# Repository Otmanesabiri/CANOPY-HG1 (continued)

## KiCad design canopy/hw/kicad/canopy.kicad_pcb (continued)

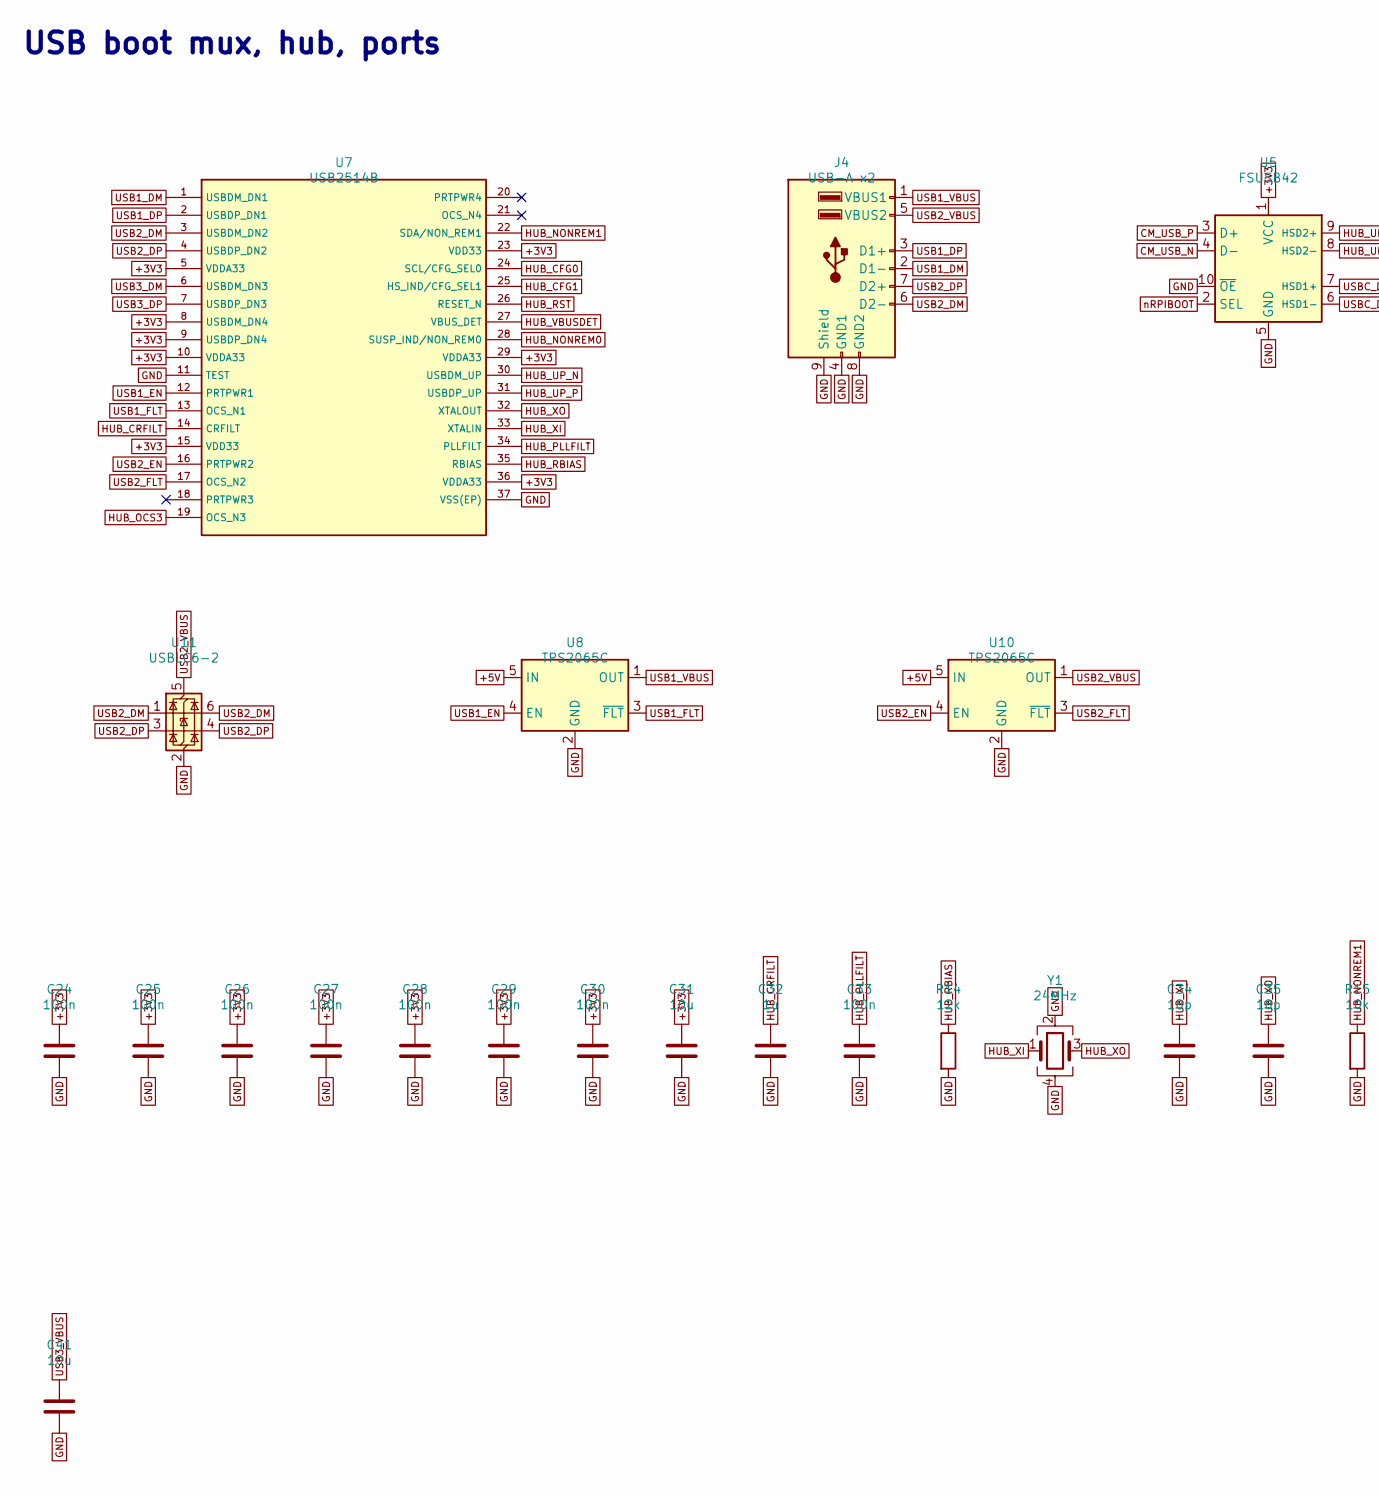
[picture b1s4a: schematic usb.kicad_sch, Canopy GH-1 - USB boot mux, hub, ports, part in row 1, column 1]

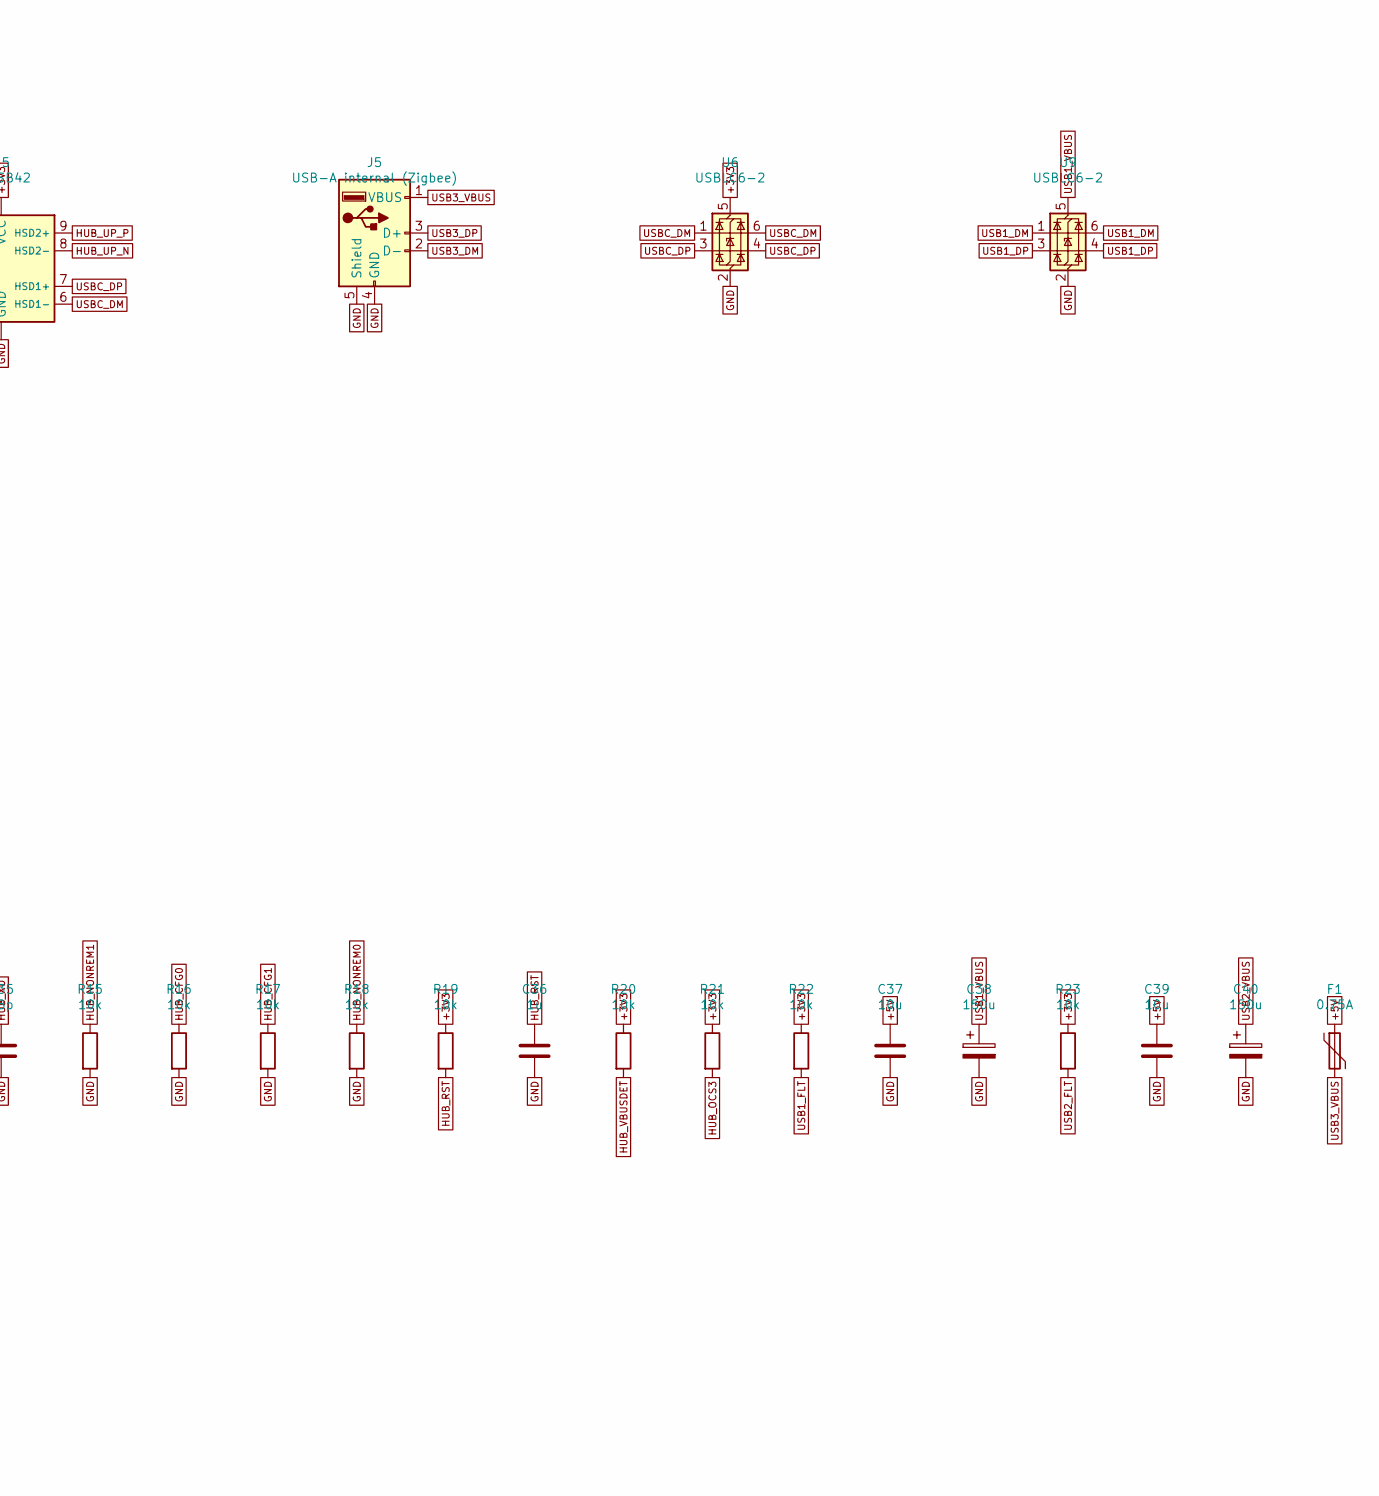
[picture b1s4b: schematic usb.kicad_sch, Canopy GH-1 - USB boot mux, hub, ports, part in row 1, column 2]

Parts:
C24, C25, C26, C27, C28, C29, C30, C33: 100n; C_0603_1608Metric; MPN GRM188R71H104KA93D
C31, C37, C39, C41: 10u; C_0603_1608Metric; MPN GRM188R61A106KE69D
C32, C36: 1u; C_0603_1608Metric; MPN CL10A105KB8NNNC
C34, C35: 18p; C_0603_1608Metric; MPN GRM1885C1H180JA01D
C38, C40: 150u; CP_EIA-3528-21_Kemet-B; MPN T520B157M006ATE070
F1: 0.75A; Fuse_1206_3216Metric; MPN 1206L075THYR
J4: USB-A x2; USB_A_Wuerth_61400826021_Horizontal_Stacked; MPN 61400826021
J5: USB-A internal (Zigbee); USB_A_Molex_105057_Vertical; MPN 105057-0001
R14: 12k; R_0603_1608Metric; MPN RC0603FR-0712KL
R15, R16, R17, R18, R19, R20, R21, R22, R23: 10k; R_0603_1608Metric; MPN RC0603FR-0710KL
U5: FSUSB42; MSOP-10_3x3mm_P0.5mm; MPN FSUSB42MUX
U6, U9, U11: USBLC6-2; SOT-23-6; MPN USBLC6-2SC6
U7: USB2514B; QFN-36-1EP_6x6mm_P0.5mm_EP3.7x3.7mm; MPN USB2514B-I/M2
U8, U10: TPS2065C; SOT-23-5; MPN TPS2065CDBVR
Y1: 24MHz; Crystal_SMD_3225-4Pin_3.2x2.5mm; MPN ABM8-24.000MHZ-B2-T

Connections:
+3V3: C24.1, C25.1, C26.1, C27.1, C28.1, C29.1, C30.1, C31.1, R19.1, R20.1, R21.1, R22.1, R23.1, U5.1 (VCC), U6.5 (VBUS), U7.5 (VDDA33), U7.8 (USBDM_DN4), U7.9 (USBDP_DN4), U7.10 (VDDA33), U7.15 (VDD33), U7.23 (VDD33), U7.29 (VDDA33), U7.36 (VDDA33); also elsewhere on the board
+5V: C37.1, C39.1, F1.1, U8.5 (IN), U10.5 (IN); also elsewhere on the board
CM_USB_N: U5.4 (D-); also elsewhere on the board
CM_USB_P: U5.3 (D+); also elsewhere on the board
GND: C24.2, C25.2, C26.2, C27.2, C28.2, C29.2, C30.2, C31.2, C32.2, C33.2, C34.2, C35.2, C36.2, C37.2, C38.2, C39.2, C40.2, C41.2, J4.4 (GND1), J4.8 (GND2), J4.9 (Shield), J5.4 (GND), J5.5 (Shield), R14.2, R15.2, R16.2, R17.2, R18.2, U5.5 (GND), U5.10 (~OE), U6.2 (GND), U7.11 (TEST), U7.37 (VSS(EP)), U8.2 (GND), U9.2 (GND), U10.2 (GND), U11.2 (GND), Y1.2, Y1.4; also elsewhere on the board
HUB_CFG0: R16.1, U7.24 (SCL/CFG_SEL0)
HUB_CFG1: R17.1, U7.25 (HS_IND/CFG_SEL1)
HUB_CRFILT: C32.1, U7.14 (CRFILT)
HUB_NONREM0: R18.1, U7.28 (SUSP_IND/NON_REM0)
HUB_NONREM1: R15.1, U7.22 (SDA/NON_REM1)
HUB_OCS3: R21.2, U7.19 (OCS_N3)
HUB_PLLFILT: C33.1, U7.34 (PLLFILT)
HUB_RBIAS: R14.1, U7.35 (RBIAS)
HUB_RST: C36.1, R19.2, U7.26 (RESET_N)
HUB_UP_N: U5.8 (HSD2-), U7.30 (USBDM_UP)
HUB_UP_P: U5.9 (HSD2+), U7.31 (USBDP_UP)
HUB_VBUSDET: R20.2, U7.27 (VBUS_DET)
HUB_XI: C34.1, U7.33 (XTALIN), Y1.1
HUB_XO: C35.1, U7.32 (XTALOUT), Y1.3
USB1_DM: J4.2 (D1-), U7.1 (USBDM_DN1), U9.1 (I/O1), U9.6 (I/O1)
USB1_DP: J4.3 (D1+), U7.2 (USBDP_DN1), U9.3 (I/O2), U9.4 (I/O2)
USB1_EN: U7.12 (PRTPWR1), U8.4 (EN)
USB1_FLT: R22.2, U7.13 (OCS_N1), U8.3 (~FLT)
USB1_VBUS: C38.1, J4.1 (VBUS1), U8.1 (OUT), U9.5 (VBUS)
USB2_DM: J4.6 (D2-), U7.3 (USBDM_DN2), U11.1 (I/O1), U11.6 (I/O1)
USB2_DP: J4.7 (D2+), U7.4 (USBDP_DN2), U11.3 (I/O2), U11.4 (I/O2)
USB2_EN: U7.16 (PRTPWR2), U10.4 (EN)
USB2_FLT: R23.2, U7.17 (OCS_N2), U10.3 (~FLT)
USB2_VBUS: C40.1, J4.5 (VBUS2), U10.1 (OUT), U11.5 (VBUS)
USB3_DM: J5.2 (D-), U7.6 (USBDM_DN3)
USB3_DP: J5.3 (D+), U7.7 (USBDP_DN3)
USB3_VBUS: C41.1, F1.2, J5.1 (VBUS)
USBC_DM: U5.6 (HSD1-), U6.1 (I/O1), U6.6 (I/O1); also elsewhere on the board
USBC_DP: U5.7 (HSD1+), U6.3 (I/O2), U6.4 (I/O2); also elsewhere on the board
nRPIBOOT: U5.2 (SEL); also elsewhere on the board

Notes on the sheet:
USB boot mux, hub, ports

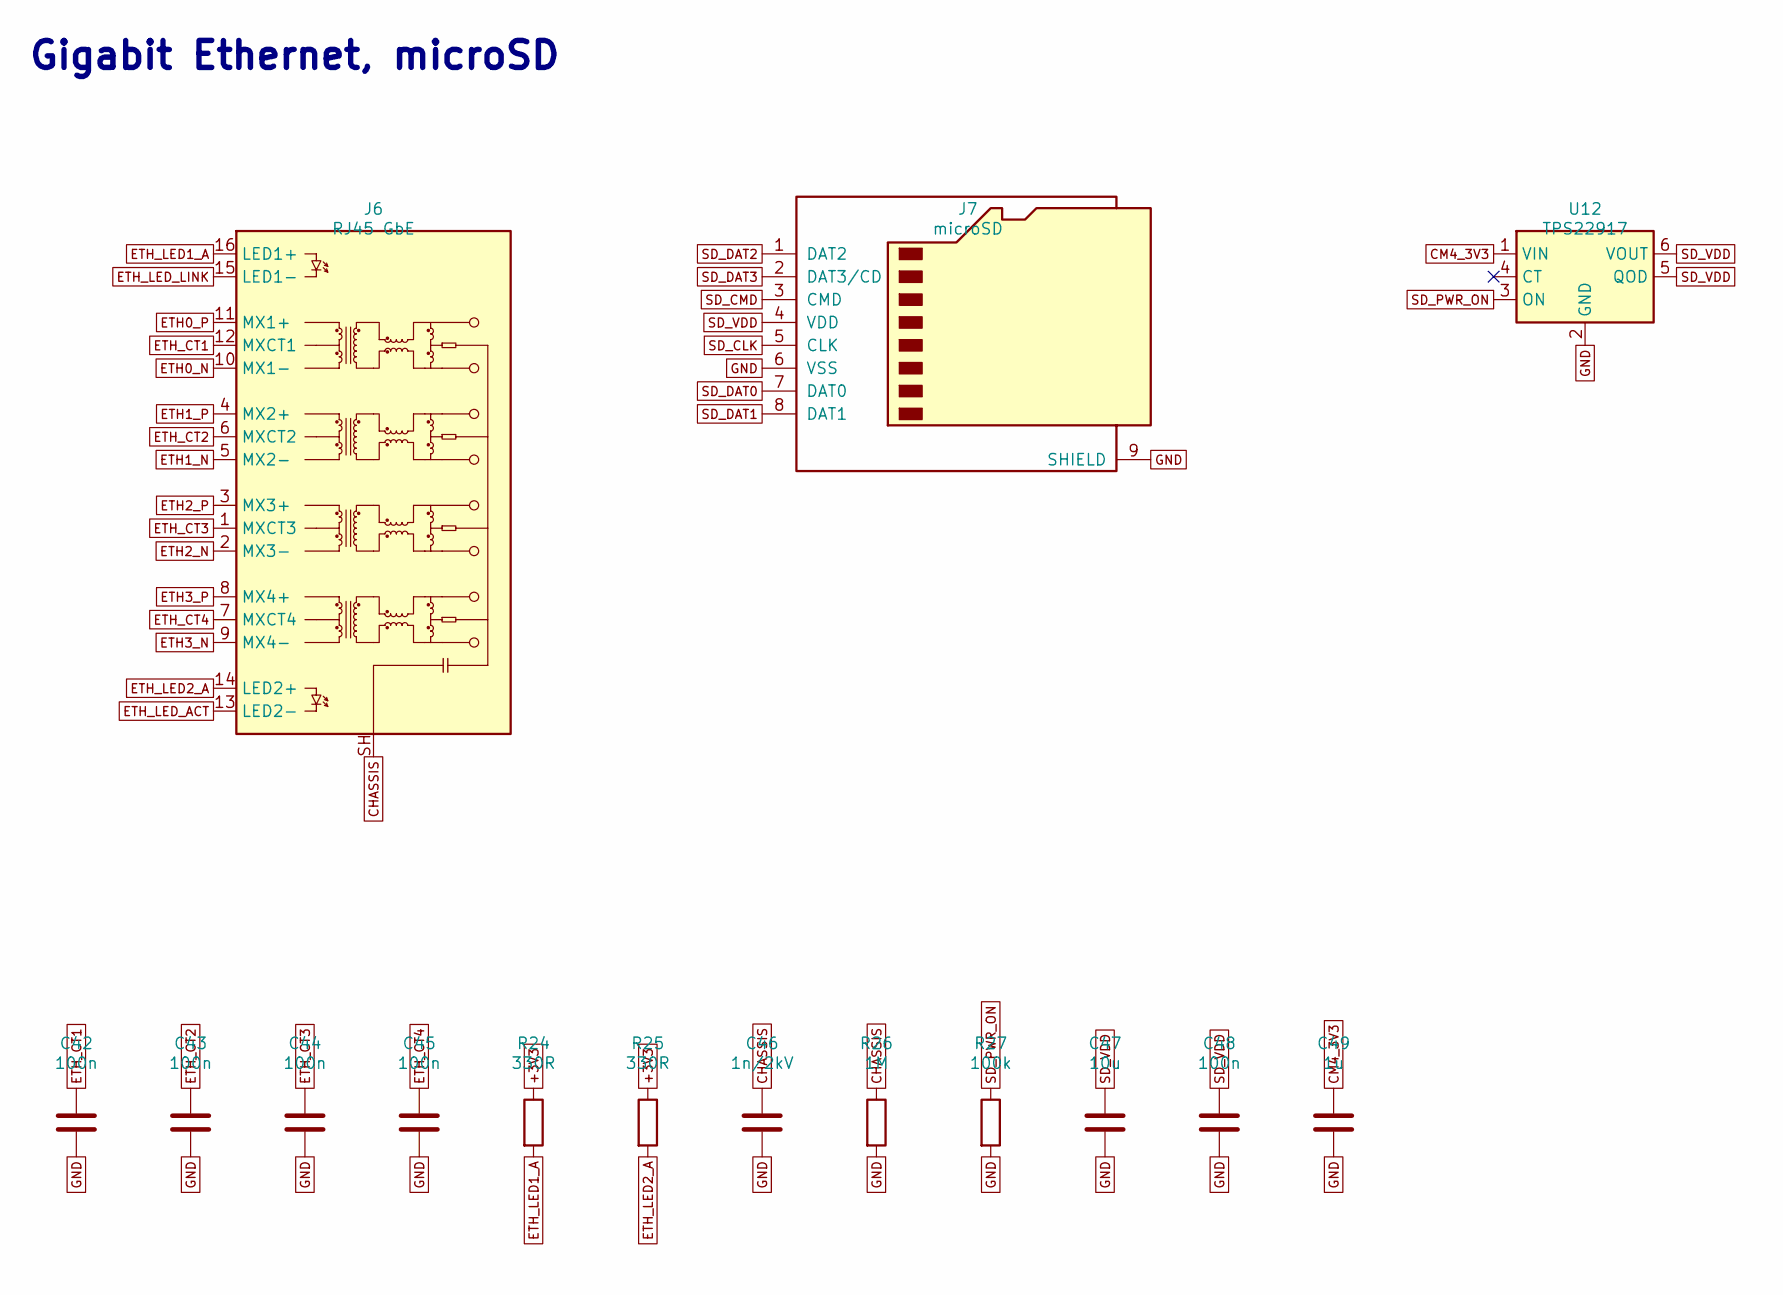
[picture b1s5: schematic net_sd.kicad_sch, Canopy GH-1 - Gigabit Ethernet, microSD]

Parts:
C42, C43, C44, C45, C48: 100n; C_0603_1608Metric; MPN GRM188R71H104KA93D
C46: 1n/2kV; C_1206_3216Metric; MPN C1206C102KGRACTU
C47: 10u; C_0603_1608Metric; MPN GRM188R61A106KE69D
C49: 1u; C_0603_1608Metric; MPN CL10A105KB8NNNC
J6: RJ45 GbE; RJ45_Pulse_JK0654219NL_Horizontal; MPN JK0654219NL
J7: microSD; microSD_HC_Molex_104031-0811; MPN 104031-0811
R24, R25: 330R; R_0603_1608Metric; MPN RC0603FR-07330RL
R26: 1M; R_0603_1608Metric; MPN RC0603FR-071ML
R27: 100k; R_0603_1608Metric; MPN RC0603FR-07100KL
U12: TPS22917; SOT-23-6; MPN TPS22917DBVR

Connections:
+3V3: R24.1, R25.1; also elsewhere on the board
CHASSIS: C46.1, J6.SH, R26.1
CM4_3V3: C49.1, U12.1 (VIN); also elsewhere on the board
ETH0_N: J6.10 (MX1-); also elsewhere on the board
ETH0_P: J6.11 (MX1+); also elsewhere on the board
ETH1_N: J6.5 (MX2-); also elsewhere on the board
ETH1_P: J6.4 (MX2+); also elsewhere on the board
ETH2_N: J6.2 (MX3-); also elsewhere on the board
ETH2_P: J6.3 (MX3+); also elsewhere on the board
ETH3_N: J6.9 (MX4-); also elsewhere on the board
ETH3_P: J6.8 (MX4+); also elsewhere on the board
ETH_CT1: C42.1, J6.12 (MXCT1)
ETH_CT2: C43.1, J6.6 (MXCT2)
ETH_CT3: C44.1, J6.1 (MXCT3)
ETH_CT4: C45.1, J6.7 (MXCT4)
ETH_LED1_A: J6.16 (LED1+), R24.2
ETH_LED2_A: J6.14 (LED2+), R25.2
ETH_LED_ACT: J6.13 (LED2-); also elsewhere on the board
ETH_LED_LINK: J6.15 (LED1-); also elsewhere on the board
GND: C42.2, C43.2, C44.2, C45.2, C46.2, C47.2, C48.2, C49.2, J7.6 (VSS), J7.9 (SHIELD), J7.10, J7.11, R26.2, R27.2, U12.2 (GND); also elsewhere on the board
SD_CLK: J7.5 (CLK); also elsewhere on the board
SD_CMD: J7.3 (CMD); also elsewhere on the board
SD_DAT0: J7.7 (DAT0); also elsewhere on the board
SD_DAT1: J7.8 (DAT1); also elsewhere on the board
SD_DAT2: J7.1 (DAT2); also elsewhere on the board
SD_DAT3: J7.2 (DAT3/CD); also elsewhere on the board
SD_PWR_ON: R27.1, U12.3 (ON); also elsewhere on the board
SD_VDD: C47.1, C48.1, J7.4 (VDD), U12.5 (QOD), U12.6 (VOUT)

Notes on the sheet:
Gigabit Ethernet, microSD

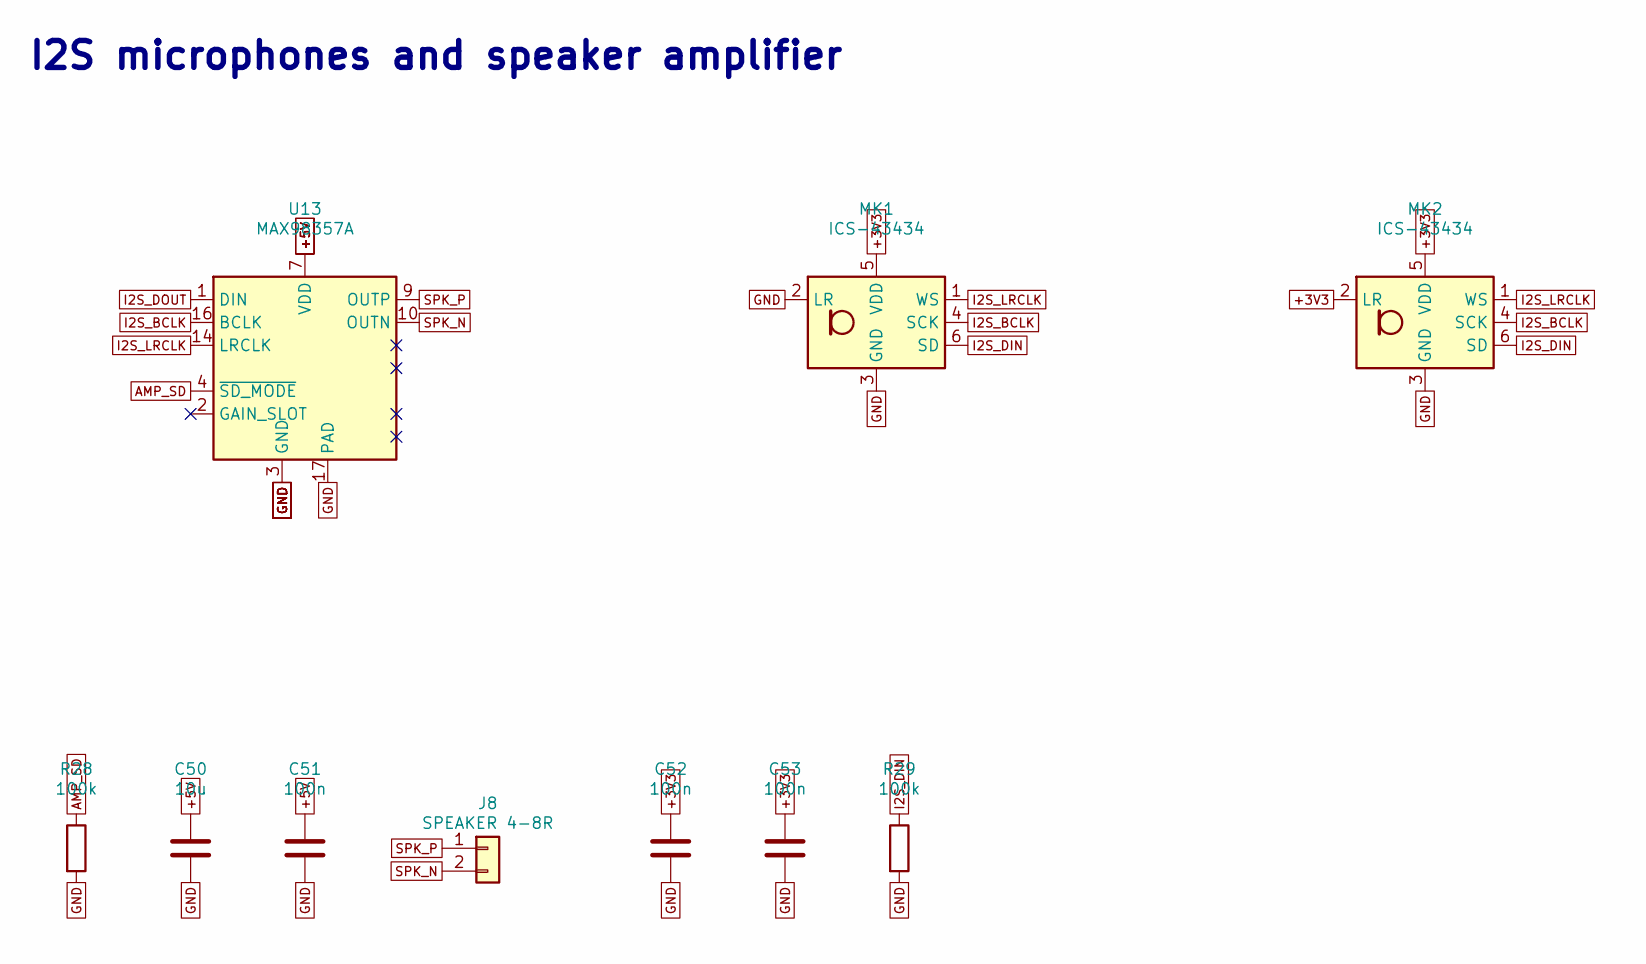
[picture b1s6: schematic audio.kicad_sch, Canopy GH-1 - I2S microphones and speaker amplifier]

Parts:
C50: 10u; C_0603_1608Metric; MPN GRM188R61A106KE69D
C51, C52, C53: 100n; C_0603_1608Metric; MPN GRM188R71H104KA93D
J8: SPEAKER 4-8R; JST_PH_S2B-PH-K_1x02_P2.00mm_Horizontal; MPN S2B-PH-K-S(LF)(SN)
MK1, MK2: ICS-43434; InvenSense_ICS-43434-6_3.5x2.65mm; MPN ICS-43434
R28, R29: 100k; R_0603_1608Metric; MPN RC0603FR-07100KL
U13: MAX98357A; TQFN-16-1EP_3x3mm_P0.5mm_EP1.23x1.23mm; MPN MAX98357AETE+T

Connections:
+3V3: C52.1, C53.1, MK1.5 (VDD), MK2.2 (LR), MK2.5 (VDD); also elsewhere on the board
+5V: C50.1, C51.1, U13.7 (VDD), U13.8 (VDD); also elsewhere on the board
AMP_SD: R28.1, U13.4 (~SD_MODE); also elsewhere on the board
GND: C50.2, C51.2, C52.2, C53.2, MK1.2 (LR), MK1.3 (GND), MK2.3 (GND), R28.2, R29.2, U13.3 (GND), U13.11 (GND), U13.15 (GND), U13.17 (PAD); also elsewhere on the board
I2S_BCLK: MK1.4 (SCK), MK2.4 (SCK), U13.16 (BCLK); also elsewhere on the board
I2S_DIN: MK1.6 (SD), MK2.6 (SD), R29.1; also elsewhere on the board
I2S_DOUT: U13.1 (DIN); also elsewhere on the board
I2S_LRCLK: MK1.1 (WS), MK2.1 (WS), U13.14 (LRCLK); also elsewhere on the board
SPK_N: J8.2, U13.10 (OUTN)
SPK_P: J8.1, U13.9 (OUTP)

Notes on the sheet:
I2S microphones and speaker amplifier

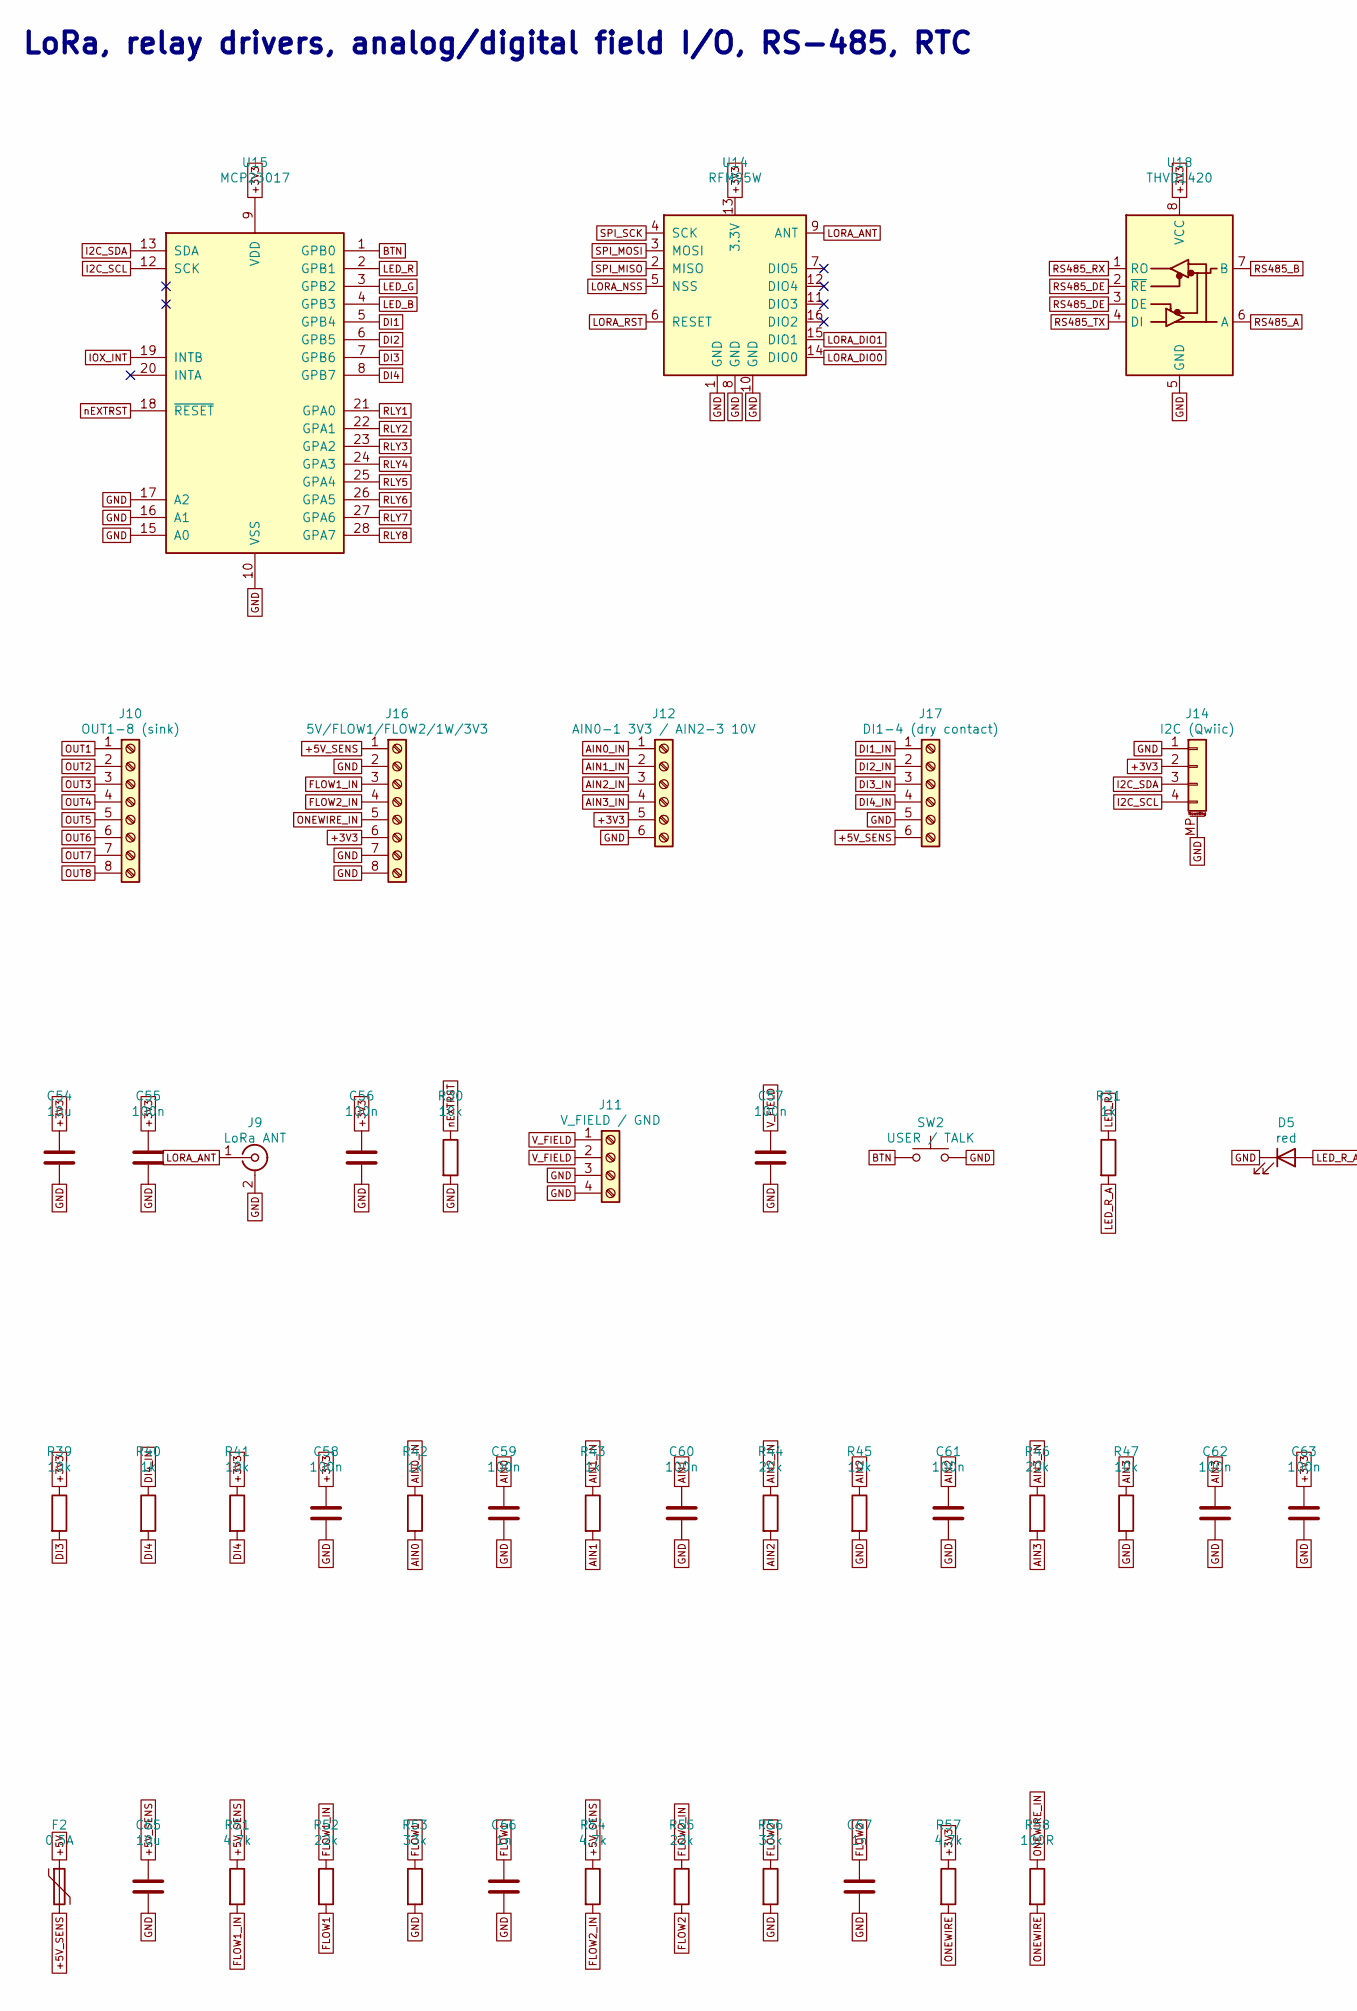
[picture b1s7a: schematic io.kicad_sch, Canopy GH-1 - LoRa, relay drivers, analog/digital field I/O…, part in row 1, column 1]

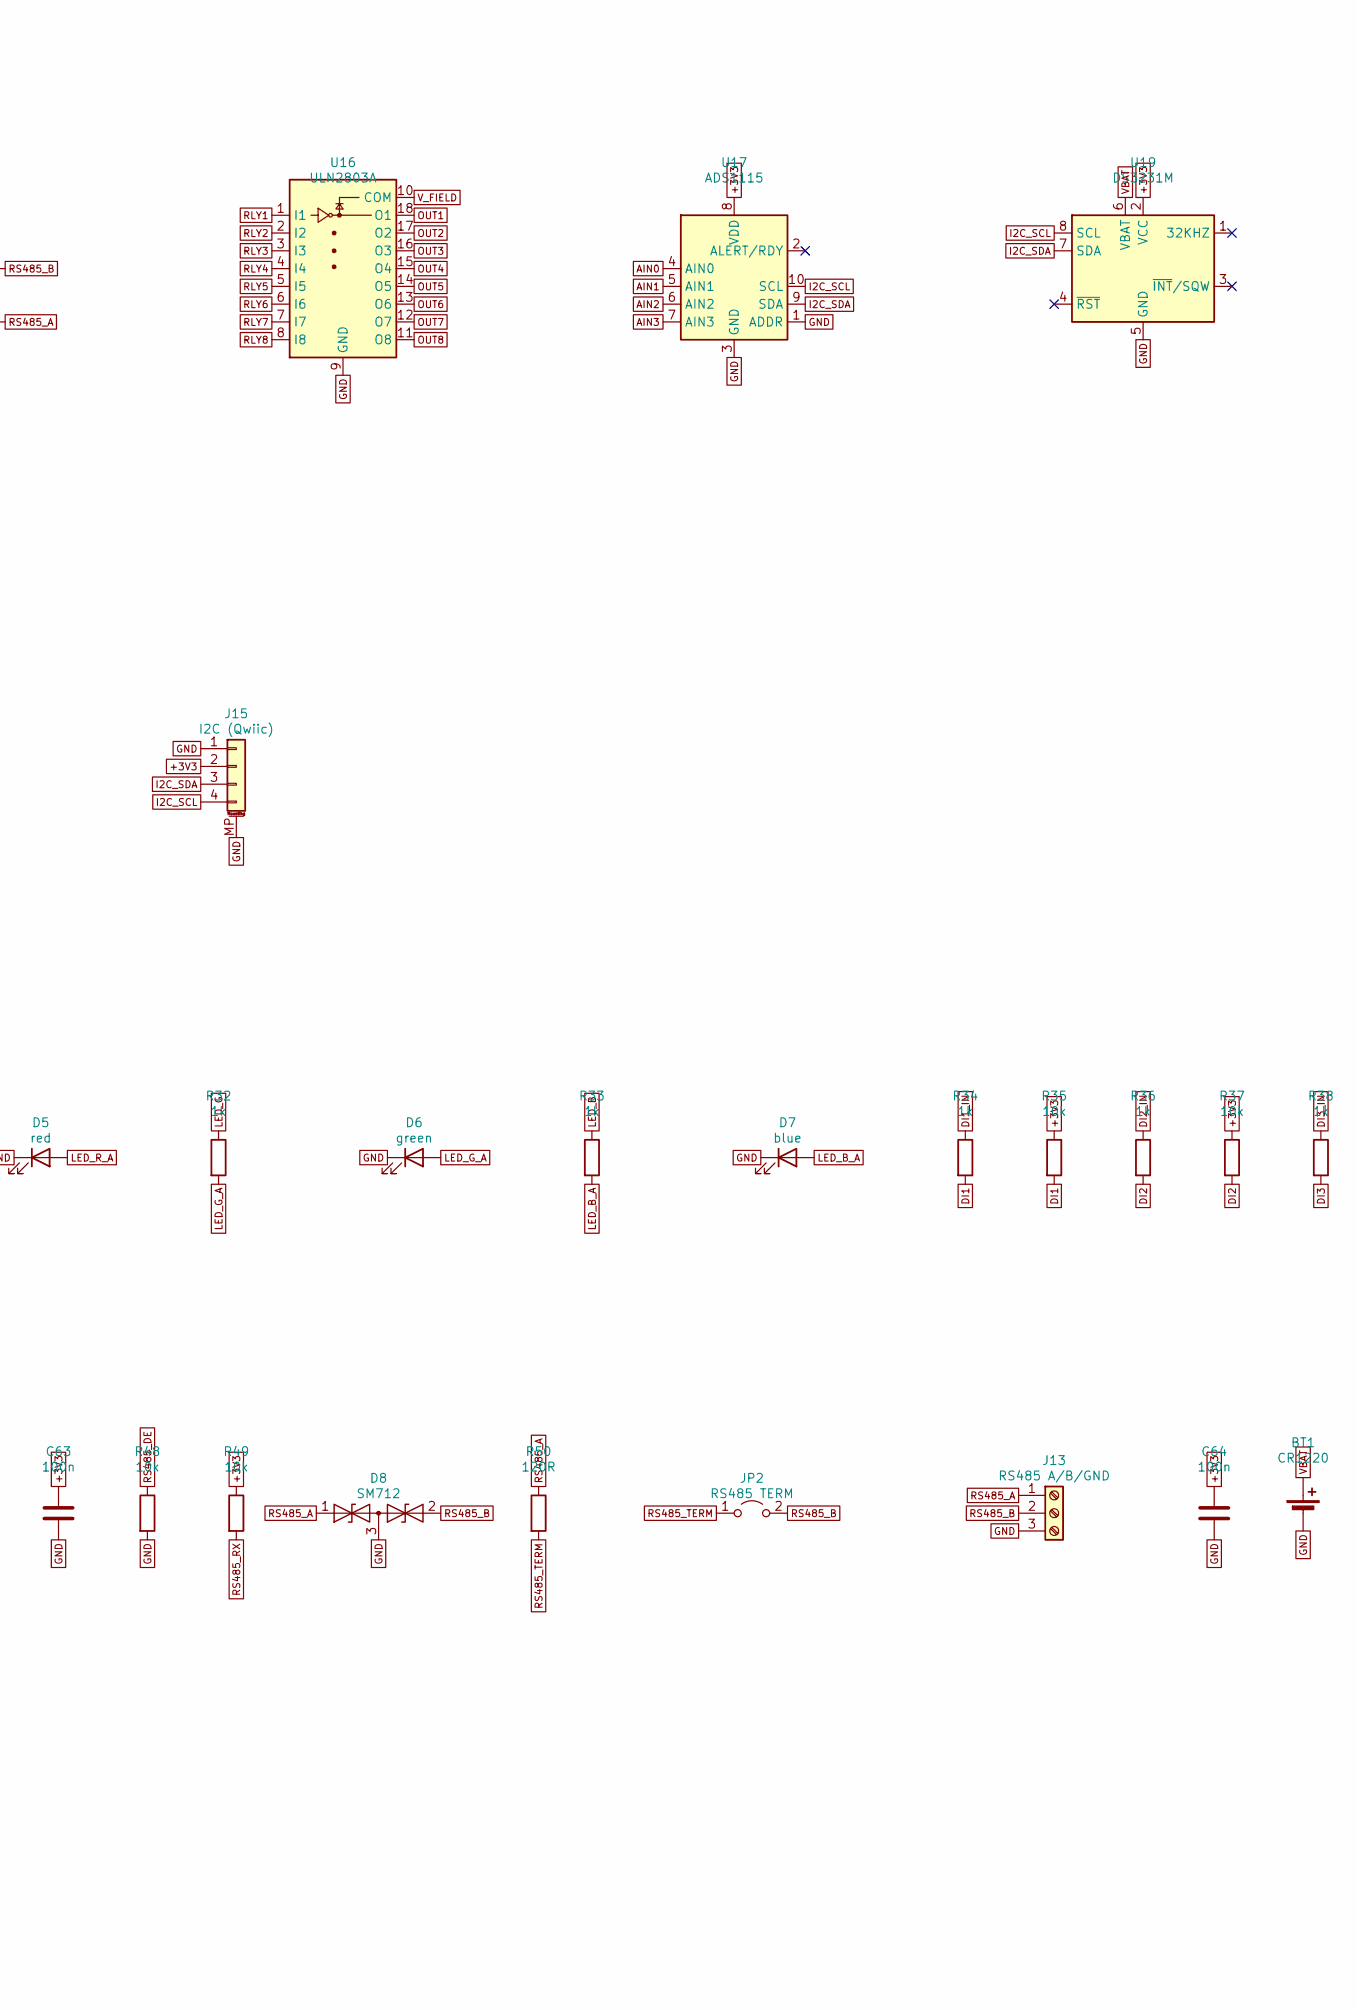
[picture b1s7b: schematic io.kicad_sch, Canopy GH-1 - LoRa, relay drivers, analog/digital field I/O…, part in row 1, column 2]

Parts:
BT1: CR1220; BatteryHolder_Keystone_3000_1x12mm; MPN 3000
C54, C65: 10u; C_0603_1608Metric; MPN GRM188R61A106KE69D
C55, C56, C57, C58, C59, C60, C61, C62, C63, C64: 100n; C_0603_1608Metric; MPN GRM188R71H104KA93D
C66, C67: 1n; C_0603_1608Metric; MPN GRM188R71H102KA01D
D5: red; LED_0603_1608Metric; MPN LTST-C191KRKT
D6: green; LED_0603_1608Metric; MPN LTST-C191KGKT
D7: blue; LED_0603_1608Metric; MPN LTST-C191TBKT
D8: SM712; SOT-23; MPN SM712.TCT
F2: 0.5A; Fuse_1206_3216Metric; MPN 0ZCJ0050FF2G
J9: LoRa ANT; U.FL_Hirose_U.FL-R-SMT-1_Vertical; MPN U.FL-R-SMT-1(10)
J10: OUT1-8 (sink); TerminalBlock_Phoenix_PT-1,5-8-3.5-H_1x08_P3.50mm_Horizontal; MPN PT 1,5/8-3,5-H (1984675)
J11: V_FIELD / GND; TerminalBlock_Phoenix_PT-1,5-4-3.5-H_1x04_P3.50mm_Horizontal; MPN PT 1,5/4-3,5-H (1984633)
J12: AIN0-1 3V3 / AIN2-3 10V; TerminalBlock_Phoenix_PT-1,5-6-3.5-H_1x06_P3.50mm_Horizontal; MPN PT 1,5/6-3,5-H (1984659)
J13: RS485 A/B/GND; TerminalBlock_Phoenix_PT-1,5-3-3.5-H_1x03_P3.50mm_Horizontal; MPN PT 1,5/3-3,5-H (1984620)
J14, J15: I2C (Qwiic); JST_SH_SM04B-SRSS-TB_1x04-1MP_P1.00mm_Horizontal; MPN SM04B-SRSS-TB(LF)(SN)
J16: 5V/FLOW1/FLOW2/1W/3V3; TerminalBlock_Phoenix_PT-1,5-8-3.5-H_1x08_P3.50mm_Horizontal; MPN PT 1,5/8-3,5-H (1984675)
J17: DI1-4 (dry contact); TerminalBlock_Phoenix_PT-1,5-6-3.5-H_1x06_P3.50mm_Horizontal; MPN PT 1,5/6-3,5-H (1984659)
JP2: RS485 TERM; PinHeader_1x02_P2.54mm_Vertical; MPN M20-9990245
R30, R35, R37, R39, R41, R45, R47, R48, R49: 10k; R_0603_1608Metric; MPN RC0603FR-0710KL
R31, R32, R33, R34, R36, R38, R40, R42, R43: 1k; R_0603_1608Metric; MPN RC0603FR-071KL
R44, R46: 20k; R_0603_1608Metric; MPN RC0603FR-0720KL
R50: 120R; R_0603_1608Metric; MPN RC0603FR-07120RL
R51, R54, R57: 4.7k; R_0603_1608Metric; MPN RC0603FR-074K7L
R52, R55: 22k; R_0603_1608Metric; MPN RC0603FR-0722KL
R53, R56: 33k; R_0603_1608Metric; MPN RC0603FR-0733KL
R58: 100R; R_0603_1608Metric; MPN RC0603FR-07100RL
SW2: USER / TALK; SW_SPST_B3U-1000P; MPN B3U-1000P
U14: RFM95W; HOPERF_RFM9XW_SMD; MPN RFM95W-915S2
U15: MCP23017; SSOP-28_5.3x10.2mm_P0.65mm; MPN MCP23017-E/SS
U16: ULN2803A; SOIC-18W_7.5x11.6mm_P1.27mm; MPN ULN2803ADWR
U17: ADS1115; TSSOP-10_3x3mm_P0.5mm; MPN ADS1115IDGSR
U18: THVD1420; SOIC-8_3.9x4.9mm_P1.27mm; MPN THVD1420DR
U19: DS3231M; SOIC-8_3.9x4.9mm_P1.27mm; MPN DS3231MZ+TRL

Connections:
+3V3: C54.1, C55.1, C56.1, C58.1, C63.1, C64.1, J12.5, J14.2, J15.2, J16.6, R35.1, R37.1, R39.1, R41.1, R49.1, R57.1, U14.13 (3.3V), U15.9 (VDD), U17.8 (VDD), U18.8 (VCC), U19.2 (VCC); also elsewhere on the board
+5V: F2.1; also elsewhere on the board
+5V_SENS: C65.1, F2.2, J16.1, J17.6, R51.1, R54.1
AIN0: C59.1, R42.2, U17.4 (AIN0)
AIN0_IN: J12.1, R42.1
AIN1: C60.1, R43.2, U17.5 (AIN1)
AIN1_IN: J12.2, R43.1
AIN2: C61.1, R44.2, R45.1, U17.6 (AIN2)
AIN2_IN: J12.3, R44.1
AIN3: C62.1, R46.2, R47.1, U17.7 (AIN3)
AIN3_IN: J12.4, R46.1
BTN: SW2.1, U15.1 (GPB0)
DI1: R34.2, R35.2, U15.5 (GPB4)
DI1_IN: J17.1, R34.1
DI2: R36.2, R37.2, U15.6 (GPB5)
DI2_IN: J17.2, R36.1
DI3: R38.2, R39.2, U15.7 (GPB6)
DI3_IN: J17.3, R38.1
DI4: R40.2, R41.2, U15.8 (GPB7)
DI4_IN: J17.4, R40.1
FLOW1: C66.1, R52.2, R53.1; also elsewhere on the board
FLOW1_IN: J16.3, R51.2, R52.1
FLOW2: C67.1, R55.2, R56.1; also elsewhere on the board
FLOW2_IN: J16.4, R54.2, R55.1
GND: BT1.2 (-), C54.2, C55.2, C56.2, C57.2, C58.2, C59.2, C60.2, C61.2, C62.2, C63.2, C64.2, C65.2, C66.2, C67.2, D5.1 (K), D6.1 (K), D7.1 (K), D8.3 (common), J9.2 (Ext), J11.3, J11.4, J12.6, J13.3, J14.1, J14.MP (MountPin), J15.1, J15.MP (MountPin), J16.2, J16.7, J16.8, J17.5, R30.2, R45.2, R47.2, R48.2, R53.2, R56.2, SW2.2, U14.1 (GND), U14.8 (GND), U14.10 (GND), U15.10 (VSS), U15.15 (A0), U15.16 (A1), U15.17 (A2), U16.9 (GND), U17.1 (ADDR), U17.3 (GND), U18.5 (GND), U19.5 (GND); also elsewhere on the board
I2C_SCL: J14.4, J15.4, U15.12 (SCK), U17.10 (SCL), U19.8 (SCL); also elsewhere on the board
I2C_SDA: J14.3, J15.3, U15.13 (SDA), U17.9 (SDA), U19.7 (SDA); also elsewhere on the board
IOX_INT: U15.19 (INTB); also elsewhere on the board
LED_B: R33.1, U15.4 (GPB3)
LED_B_A: D7.2 (A), R33.2
LED_G: R32.1, U15.3 (GPB2)
LED_G_A: D6.2 (A), R32.2
LED_R: R31.1, U15.2 (GPB1)
LED_R_A: D5.2 (A), R31.2
LORA_ANT: J9.1 (In), U14.9 (ANT)
LORA_DIO0: U14.14 (DIO0); also elsewhere on the board
LORA_DIO1: U14.15 (DIO1); also elsewhere on the board
LORA_NSS: U14.5 (NSS); also elsewhere on the board
LORA_RST: U14.6 (RESET); also elsewhere on the board
ONEWIRE: R57.2, R58.2; also elsewhere on the board
ONEWIRE_IN: J16.5, R58.1
OUT1: J10.1, U16.18 (O1)
OUT2: J10.2, U16.17 (O2)
OUT3: J10.3, U16.16 (O3)
OUT4: J10.4, U16.15 (O4)
OUT5: J10.5, U16.14 (O5)
OUT6: J10.6, U16.13 (O6)
OUT7: J10.7, U16.12 (O7)
OUT8: J10.8, U16.11 (O8)
RLY1: U15.21 (GPA0), U16.1 (I1)
RLY2: U15.22 (GPA1), U16.2 (I2)
RLY3: U15.23 (GPA2), U16.3 (I3)
RLY4: U15.24 (GPA3), U16.4 (I4)
RLY5: U15.25 (GPA4), U16.5 (I5)
RLY6: U15.26 (GPA5), U16.6 (I6)
RLY7: U15.27 (GPA6), U16.7 (I7)
RLY8: U15.28 (GPA7), U16.8 (I8)
RS485_A: D8.1 (A1), J13.1, R50.1, U18.6 (A)
RS485_B: D8.2 (A2), J13.2, JP2.2 (B), U18.7 (B)
RS485_DE: R48.1, U18.2 (~RE), U18.3 (DE); also elsewhere on the board
RS485_RX: R49.2, U18.1 (RO); also elsewhere on the board
RS485_TERM: JP2.1 (A), R50.2
RS485_TX: U18.4 (DI); also elsewhere on the board
SPI_MISO: U14.2 (MISO); also elsewhere on the board
SPI_MOSI: U14.3 (MOSI); also elsewhere on the board
SPI_SCK: U14.4 (SCK); also elsewhere on the board
VBAT: BT1.1 (+), U19.6 (VBAT)
V_FIELD: C57.1, J11.1, J11.2, U16.10 (COM)
nEXTRST: R30.1, U15.18 (~RESET); also elsewhere on the board

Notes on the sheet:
LoRa, relay drivers, analog/digital field I/O, RS-485, RTC
